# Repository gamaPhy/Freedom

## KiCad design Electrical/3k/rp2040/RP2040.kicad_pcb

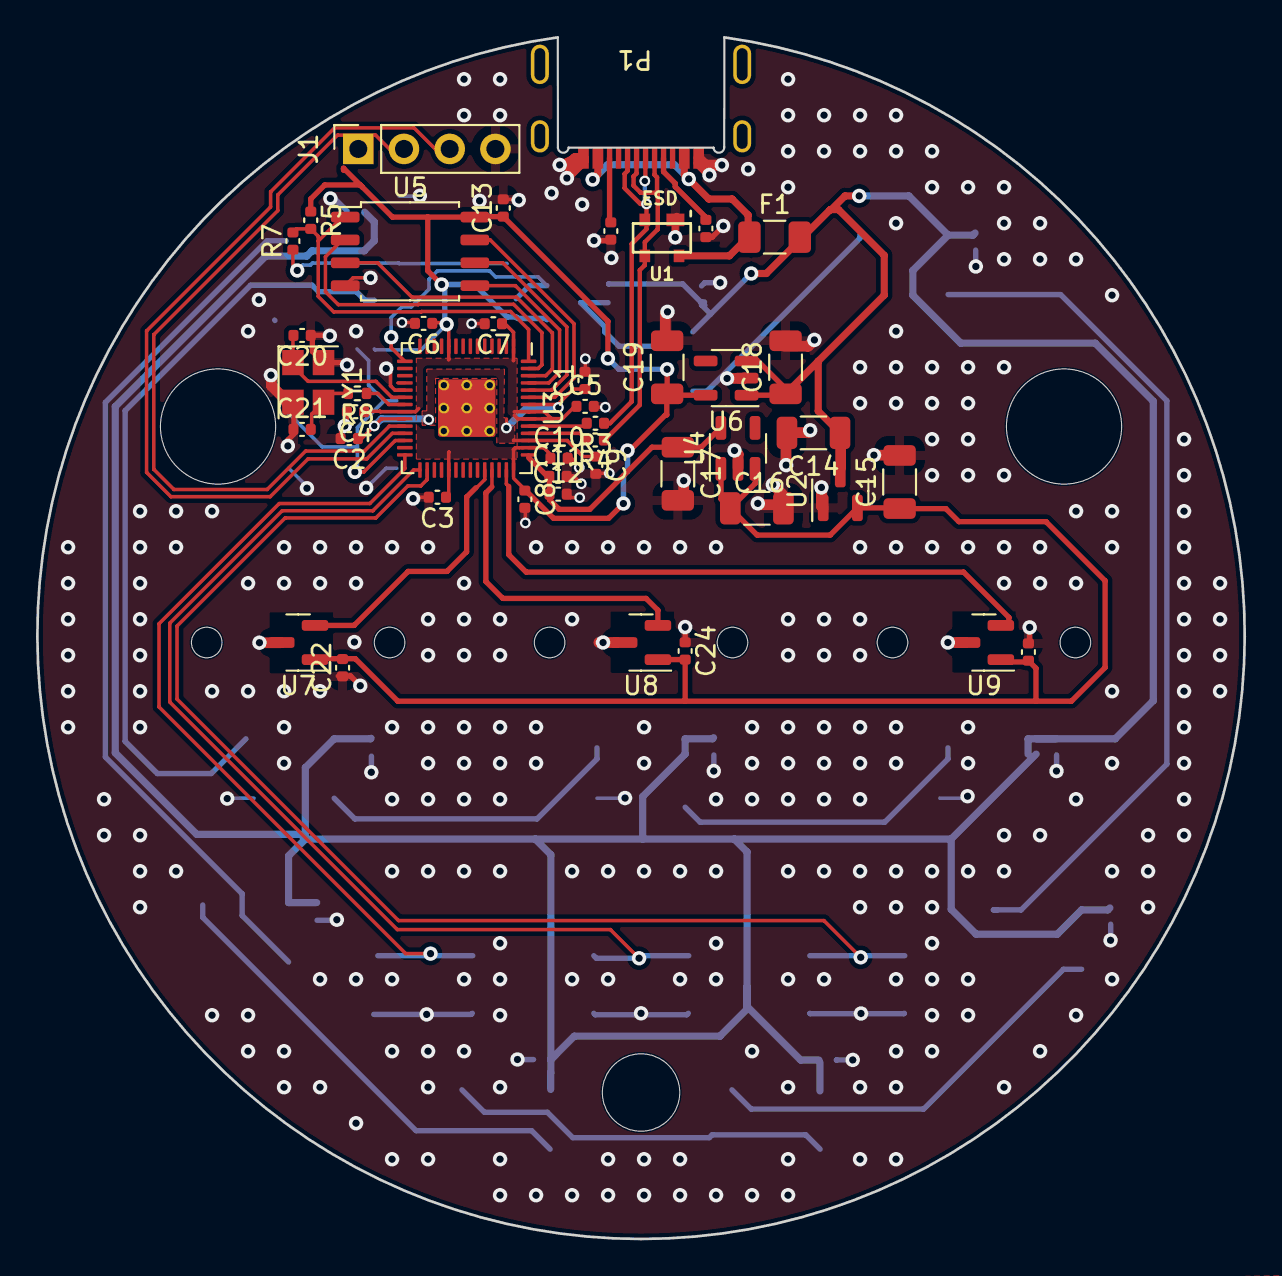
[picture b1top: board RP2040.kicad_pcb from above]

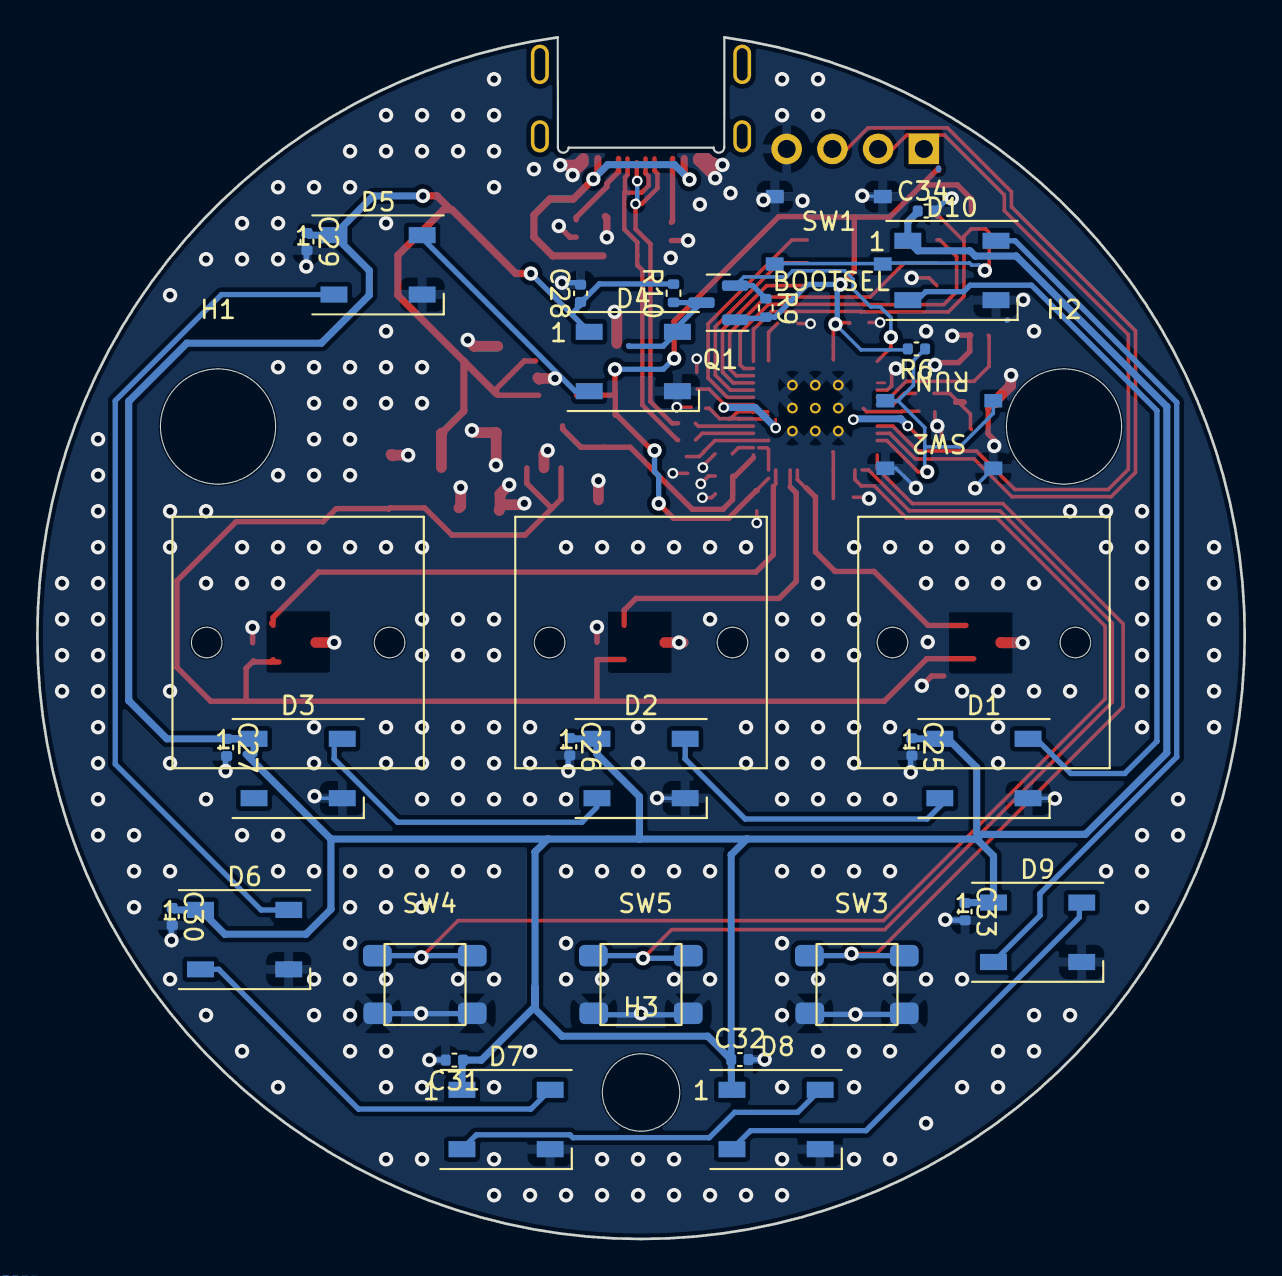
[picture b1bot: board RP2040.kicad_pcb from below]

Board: 4 copper layers, 67.1 x 66.8 mm, 76 parts (32 on the bottom side), 43 nets.

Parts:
C1, C2, C3, C4, C5, C6, C7, C8, C13, C22, C23, C24, C25, C26, C27, C28, C29, C30, C31, C32, C33, C34: 100n; C_0402_1005Metric
C9, C10, C12: 1u; C_0402_1005Metric
C11: 10n; C_0402_1005Metric
C14, C15, C16, C17, C18, C19: 10u; C_1206_3216Metric
C20, C21: 27p; C_0402_1005Metric
D1, D2, D3, D4, D5, D6, D7, D8, D9, D10: WS2812B; LED_WS2812B_PLCC4_5.0x5.0mm_P3.2mm
F1: nSMD050-24V; Fuse_1206_3216Metric
H1, H2: MountingHole_6.4mm_M6_DIN965
H3: MountingHole_4.3mm_M4_DIN965
J1: Conn_01x04_Socket; PinSocket_1x04_P2.54mm_Vertical
P1: USB-TYPE-C-016; USB-TYPE-C-016_Receptacle_DEALON_16P_MidMnt
Q1: BSS138; SOT-23
R1, R2: 5.1k; C_0402_1005Metric
R3, R4: 27R; C_0402_1005Metric
R5: 10k; C_0402_1005Metric
R6, R7: 1k; C_0402_1005Metric
R8: 47; R_0402_1005Metric
R9, R10: 10k; R_0402_1005Metric
SW1, SW2: TS-1187A-B-A-B; TS-1187A
SW3: BUTT1; PTS647_4.5x4.5mm
SW4: BUTT3; PTS647_4.5x4.5mm
SW5: BUTT2; PTS647_4.5x4.5mm
U1: PRTR5V0U2X; SOT-143B
U2: ME6208A44M3G; SOT-23
U3: RP2040; RP2040-QFN-56
U4: ME6212C25M5G; SOT-23-5
U5: W25Q16JVSS; SOIC-8_5.23x5.23mm_P1.27mm
U6: ME6212C33M5G; SOT-23-5
U7, U8, U9: SLSS49E; SOT-23
Y1: 12MHz; Crystal_SMD_3225-4Pin_3.2x2.5mm

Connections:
+1V1: C1.1, C2.1, C9.1, U3.23 (DVDD), U3.45 (VREG_VOUT), U3.50 (DVDD)
+3V3: C3.1, C4.1, C5.1, C6.1, C7.1, C8.1, C10.1, C13.1, C19.1, J1.1, Q1.1 (G), R5.1, R6.2, R9.2, U3.1 (IOVDD), U3.10 (IOVDD), U3.22 (IOVDD), U3.33 (IOVDD), U3.42 (IOVDD), U3.44 (VREG_IN), U3.48 (USB_VDD), U3.49 (IOVDD), U5.8 (VCC), U6.5 (VOUT)
+4V4: C15.1, C16.1, C22.2, C23.2, C24.2, U2.2 (VO), U4.1 (VIN), U4.3 (EN), U7.1 (VCC), U8.1 (VCC), U9.1 (VCC)
+5V: C14.1, C18.1, C25.1, C26.1, C27.1, C28.1, C29.1, C30.1, C31.1, C32.1, C33.1, C34.1, D1.1 (VDD), D2.1 (VDD), D3.1 (VDD), D4.1 (VDD), D5.1 (VDD), D6.1 (VDD), D7.1 (VDD), D8.1 (VDD), D9.1 (VDD), D10.1 (VDD), F1.2, R10.2, U2.3 (VI), U6.1 (VIN), U6.3 (EN)
/QSPI_SCLK: U3.52 (QSPI_SCLK), U5.6 (CLK)
/QSPI_SD0: U3.53 (QSPI_SD0), U5.5 (DI(IO0))
/QSPI_SD1: U3.55 (QSPI_SD1), U5.2 (DO(IO1))
/QSPI_SD2: U3.54 (QSPI_SD2), U5.3 (IO2)
/QSPI_SD3: U3.51 (QSPI_SD3), U5.7 (IO3)
/QSPI_SS: R5.2, R7.2, U3.56 (QSPI_SS), U5.1 (~CS)
ADC_AVDD: C11.1, C12.1, C17.1, U3.43 (ADC_AVDD), U4.5 (VOUT)
ADC_IN1: U3.38 (GPIO26_ADC0), U7.2 (VOUT)
ADC_IN2: U3.39 (GPIO27_ADC1), U8.2 (VOUT)
ADC_IN3: U3.41 (GPIO29_ADC3), U9.2 (VOUT)
BUTT0: SW3.1, U3.28 (GPIO17)
BUTT1: SW5.1, U3.29 (GPIO18)
BUTT2: SW4.1, U3.30 (GPIO19)
GND: C1.2, C2.2, C3.2, C4.2, C5.2, C6.2, C7.2, C8.2, C9.2, C10.2, C11.2, C12.2, C13.2, C14.2, C15.2, C16.2, C17.2, C18.2, C19.2, C20.1, C21.1, C22.1, C23.1, C24.1, C25.2, C26.2, C27.2, C28.2, C29.2, C30.2, C31.2, C32.2, C33.2, C34.2, D1.3 (VSS), D2.3 (VSS), D3.3 (VSS), D4.3 (VSS), D5.3 (VSS), D6.3 (VSS), D7.3 (VSS), D8.3 (VSS), D9.3 (VSS), D10.3 (VSS), J1.4, P1.A1 (GND), P1.A12 (GND), P1.B1 (GND), P1.B12 (GND), R1.2, R2.2, SW1.1, SW2.1, SW3.2, SW4.2, SW5.2, U1.1 (GND), U2.1 (GND), U3.19 (TESTEN), U3.57 (GND), U4.2 (GND), U5.4 (GND), U6.2 (GND), U7.3 (GND), U8.3 (GND), U9.3 (GND), Y1.2, Y1.4
LED_D: Q1.2 (S), R9.1, U3.15 (GPIO12)
unnamed: C21.2, R8.2, Y1.3
unnamed: D1.2 (DOUT), D2.4 (DIN)
unnamed: D2.2 (DOUT), D3.4 (DIN)
unnamed: D4.4 (DIN), Q1.3 (D), R10.1
unnamed: D4.2 (DOUT), D5.4 (DIN)
unnamed: D5.2 (DOUT), D6.4 (DIN)
unnamed: D6.2 (DOUT), D7.4 (DIN)
unnamed: D7.2 (DOUT), D8.4 (DIN)
unnamed: D8.2 (DOUT), D9.4 (DIN)
unnamed: D9.2 (DOUT), D10.4 (DIN)
unnamed: P1.A5 (CC1), R1.1
unnamed: P1.B5 (CC2), R2.1
unnamed: R7.1, SW1.2
unnamed: R6.1, SW2.2, U3.26 (RUN)
unnamed: R4.2, U3.46 (USB_DM)
unnamed: R3.2, U3.47 (USB_DP)
OSC_IN: C20.2, U3.20 (XIN), Y1.1
OSC_OUT: R8.1, U3.21 (XOUT)
SWCLK: J1.2, U3.24 (SWCLK)
SWDIO: J1.3, U3.25 (SWD)
UG_DIN: D1.4 (DIN), D10.2 (DOUT)
USB_D+: P1.A6 (D+), P1.B6 (D+), R3.1, U1.2 (I/O1)
USB_D-: P1.A7 (D-), P1.B7 (D-), R4.1, U1.3 (I/O2)
VBUS: F1.1, P1.A4 (VBUS), P1.A9 (VBUS), P1.B4 (VBUS), P1.B9 (VBUS), U1.4 (VCC)

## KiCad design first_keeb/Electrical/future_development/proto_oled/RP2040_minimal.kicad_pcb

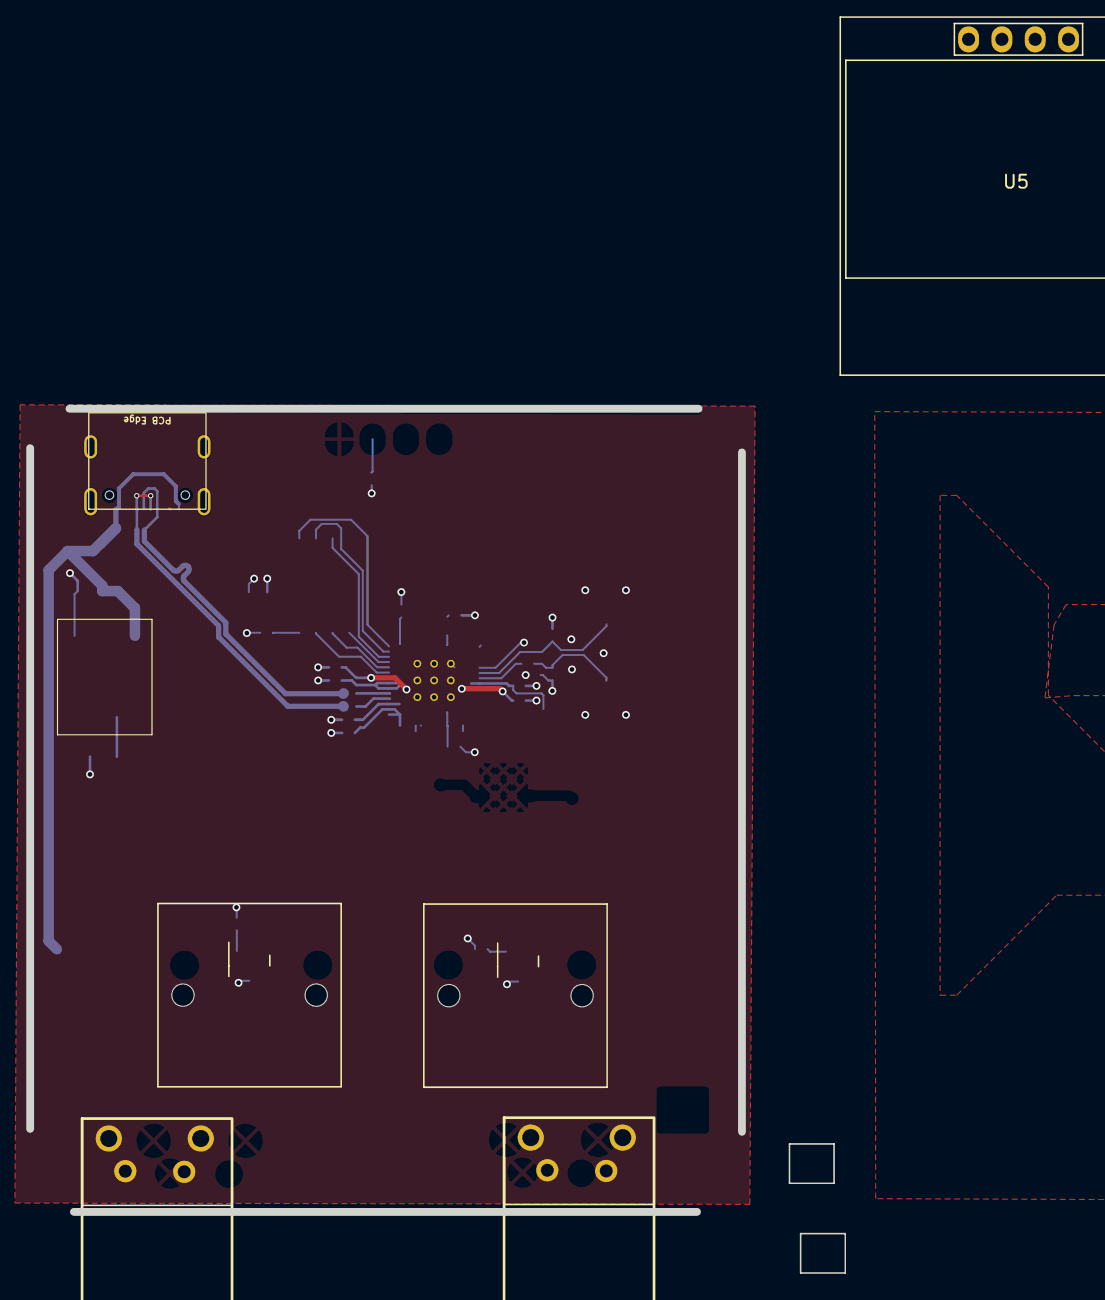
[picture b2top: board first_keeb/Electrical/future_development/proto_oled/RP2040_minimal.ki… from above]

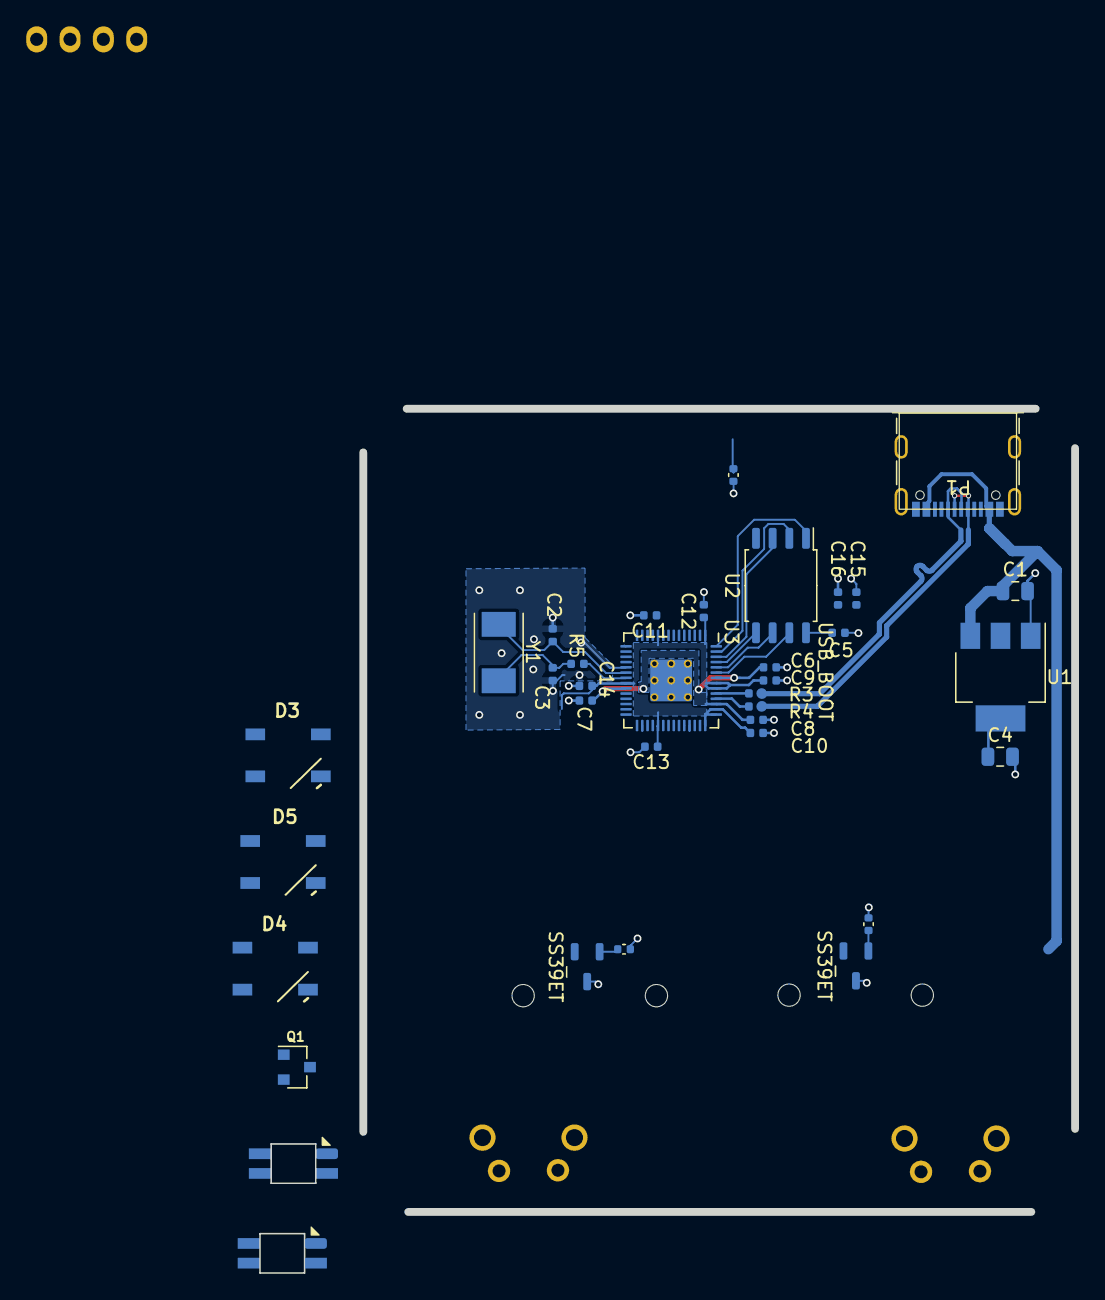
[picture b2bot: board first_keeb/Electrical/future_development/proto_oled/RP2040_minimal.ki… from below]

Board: 2 copper layers, 62.1 x 65.9 mm, 38 parts (35 on the bottom side), 21 nets.

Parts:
C1, C4: 10u; C_0805_2012Metric
C2, C3: 27p; C_0402_1005Metric
C5, C6, C7, C9, C11, C12, C13, C14, C15, C16: 100n; C_0402_1005Metric
C8, C10: 1u; C_0402_1005Metric
C21, C22, C23: C_0402_1005Metric
D1, D2: SK6812-MINI-E
D3, D4, D5: WS2812B
P1: USB_C_Receptacle_GCT_USB4105-xx-A_16P_TopMnt_Hori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; USB_C_Receptacle_GCT_USB4105-xx-A_16P_TopMnt_Horizontal
Q1: SOT-23
R3, R4: 27; C_0402_1005Metric
R5: 1k; C_0402_1005Metric
S1, S1#2: SS39ET; SOT-23-3
SW1, SW2: 2-1825027-0_Right_Angle_Switch-9.24mm_Stem; 2-1825027-0_Right_Angle_Button
U1: NCP1117-3.3_SOT223; SOT-223-3_TabPin2
U2: W25Q128JVS; SOIC-8_5.23x5.23mm_P1.27mm
U3: RP2040; RP2040-QFN-56
U5: 128x64OLED
Y1: ABLS-12.000MHZ-B4-T; Crystal_SMD_Abracon_ABM7-2Pin_6.0x3.5mm

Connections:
+1V1: C6.1, C7.1, C8.1, U3.23, U3.45, U3.50
+3V3: C4.1, C5.1, C9.1, C10.1, C11.1, C12.1, C13.1, C14.1, C15.1, C16.1, C21.1, C22.1, C23.1, S1.1, S1#2.1, U1.2, U2.8, U3.1, U3.10, U3.22, U3.33, U3.42, U3.43, U3.44, U3.48, U3.49, U5.2
/GPIO18: SW2.2, U3.29
/GPIO19: SW1.2, U3.30
/GPIO26_ADC0: S1.2, U3.38
/GPIO27_ADC1: S1#2.2, U3.39
/QSPI_SCLK: U2.6, U3.52
/QSPI_SD0: U2.5, U3.53
/QSPI_SD1: U2.2, U3.55
/QSPI_SD2: U2.3, U3.54
/QSPI_SD3: U2.7, U3.51
/QSPI_SS: U2.1, U3.56
/USB_D+: P1.A6, P1.B6, R3.1
/USB_D-: P1.A7, P1.B7, R4.1
/XIN: C2.1, U3.20, Y1.1
/XOUT: R5.1, U3.21
GND: C1.2, C2.2, C3.2, C4.2, C5.2, C6.2, C7.2, C8.2, C9.2, C10.2, C11.2, C12.2, C13.2, C14.2, C15.2, C16.2, C21.2, C22.2, C23.2, D3.3, D4.3, D5.3, P1.A1, P1.A12, P1.B1, P1.B12, S1.3, S1#2.3, SW1.1, SW1.3, SW1.4, SW2.1, SW2.3, SW2.4, U1.1, U2.4, U3.19, U3.57, U5.1
unnamed: C3.1, R5.2, Y1.2
unnamed: R3.2, U3.47
unnamed: R4.2, U3.46
VBUS: C1.1, D3.1, D4.1, D5.1, P1.A4, P1.A9, P1.B4, P1.B9, U1.3

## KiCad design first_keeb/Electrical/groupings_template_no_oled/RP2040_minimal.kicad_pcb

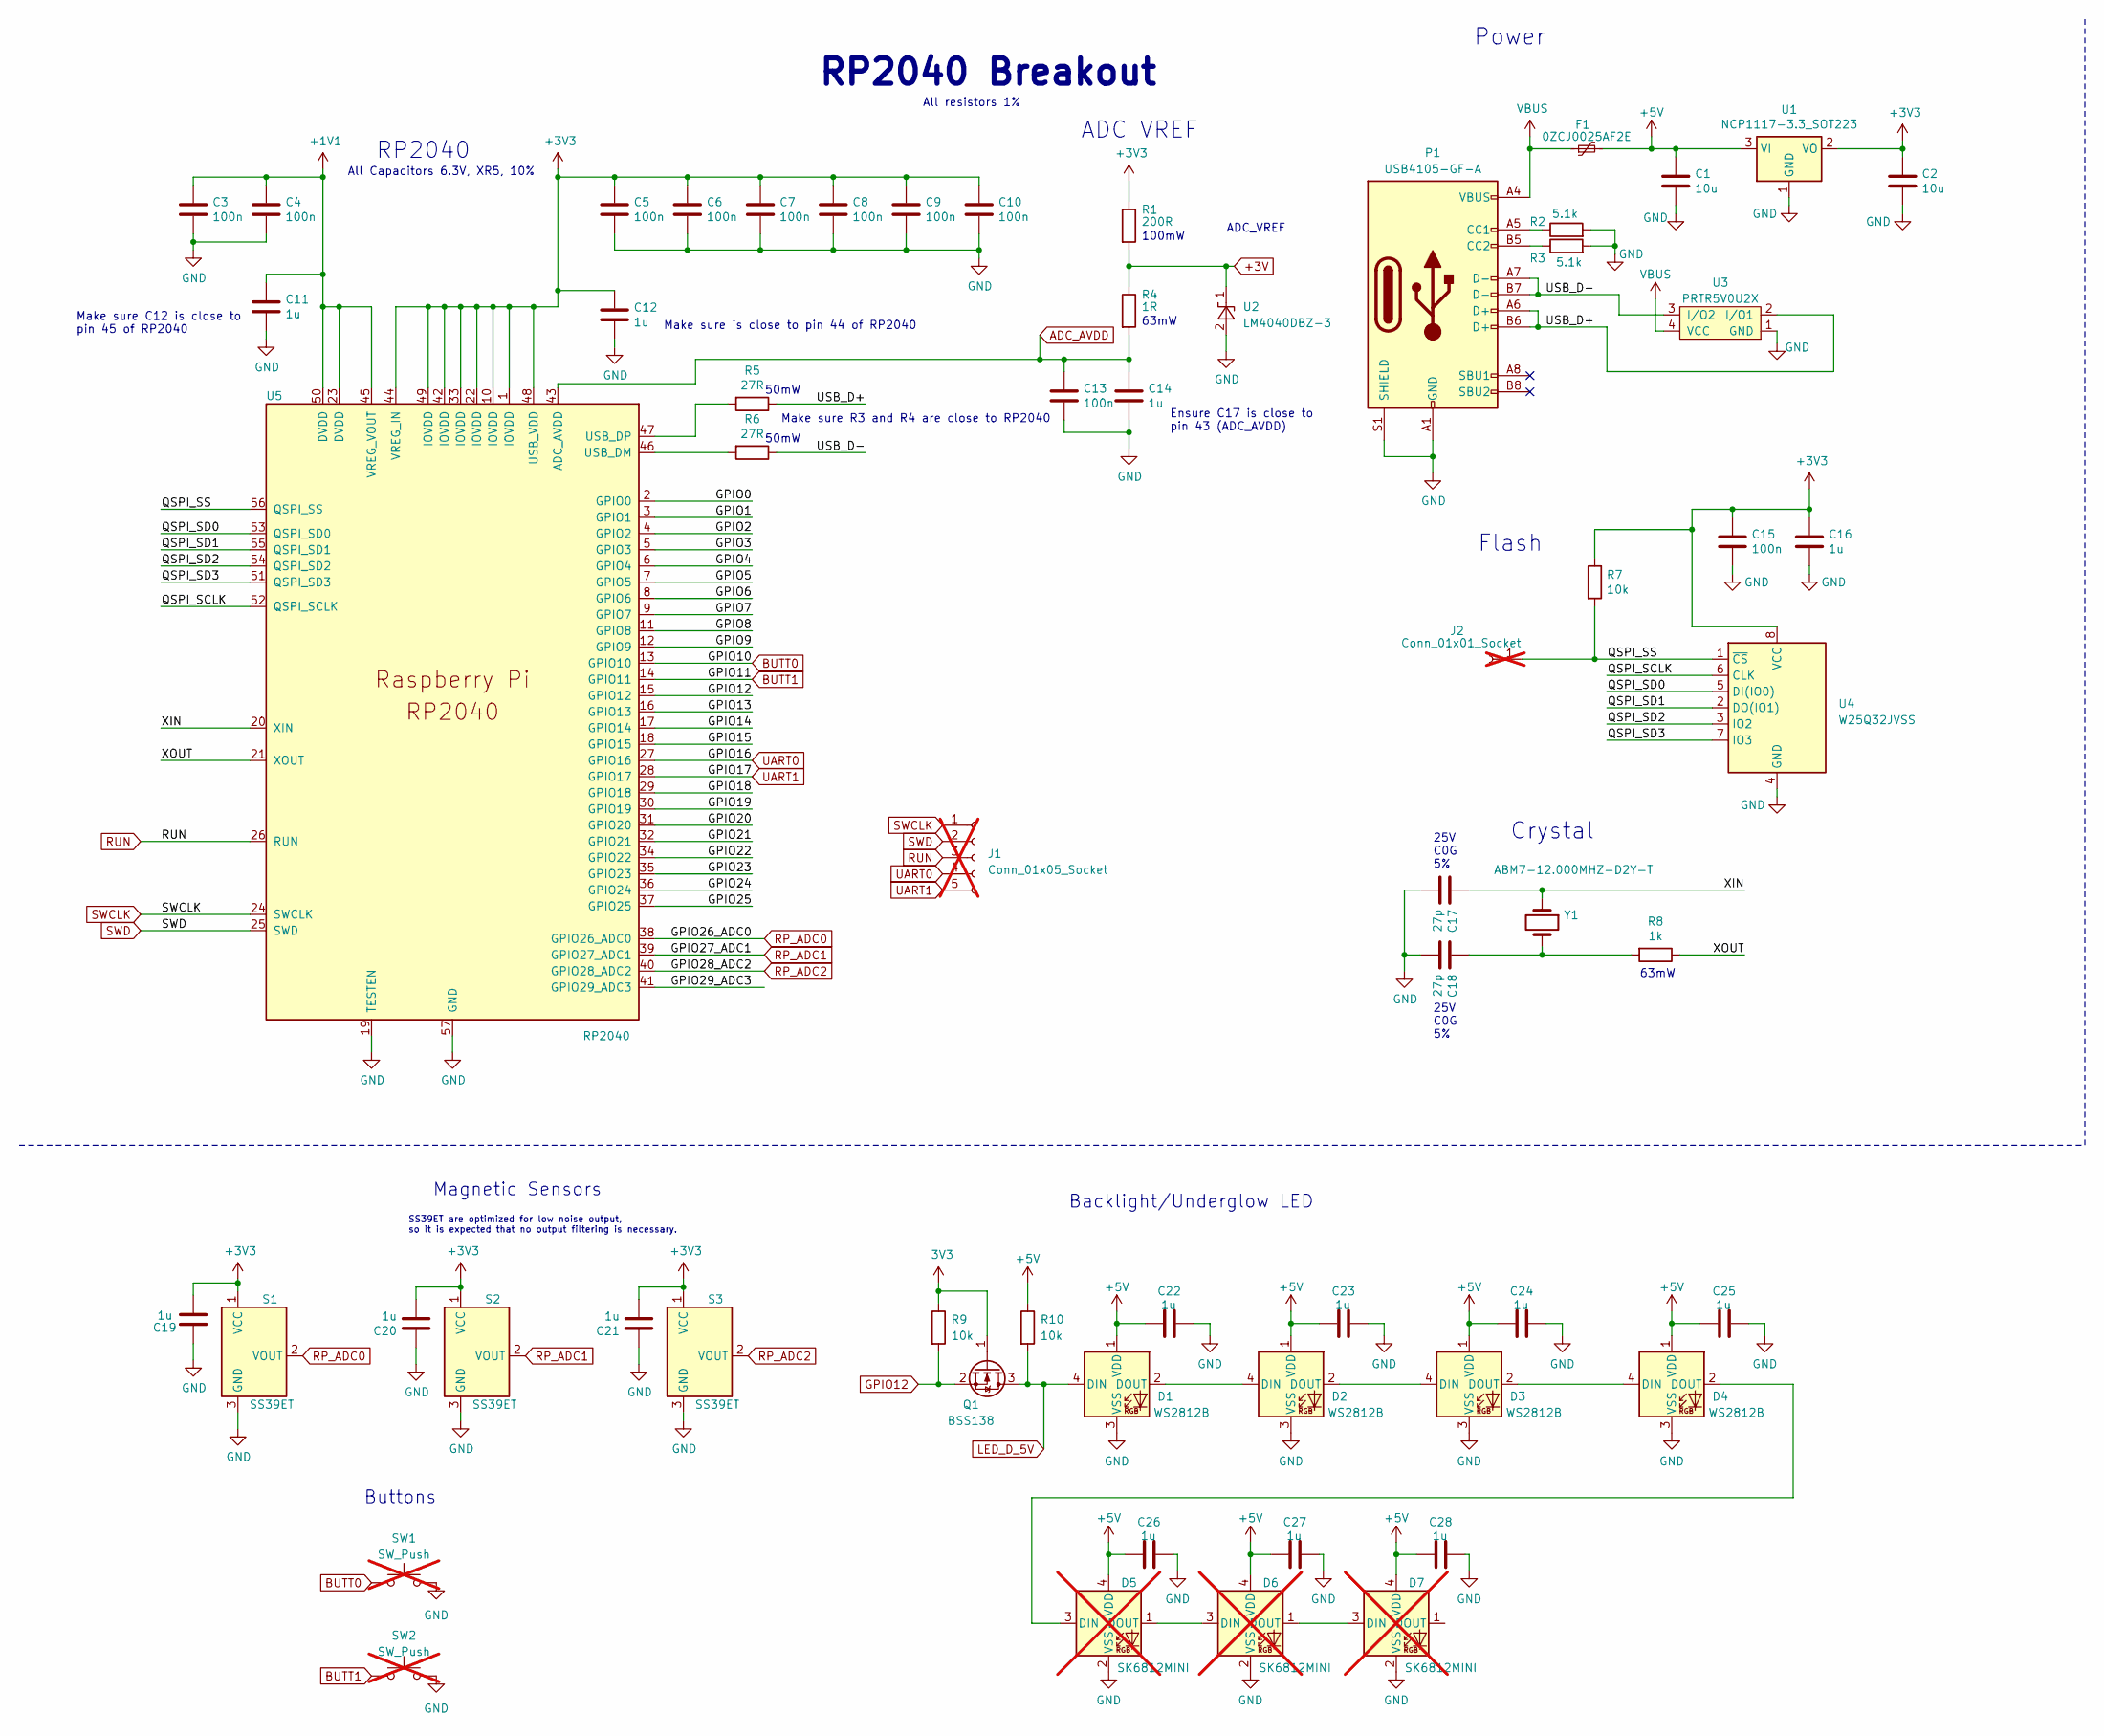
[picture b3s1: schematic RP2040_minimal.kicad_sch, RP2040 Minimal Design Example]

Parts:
C1, C2: 10u; C_0805_2012Metric
C3, C4, C5, C6, C7, C8, C9, C10, C13, C15: 100n; C_0402_1005Metric
C11, C12, C14, C16, C19, C20, C21, C22, C23, C24, C25, C26, C27, C28: 1u; C_0402_1005Metric
C17, C18: 27p; C_0402_1005Metric
D1, D2, D3, D4: WS2812B; LED_WS2812B_PLCC4_5.0x5.0mm_P3.2mm
D5, D6, D7: SK6812MINI; LED_SK6812MINI_PLCC4_3.5x3.5mm_P1.75mm; not fitted
F1: 0ZCJ0025AF2E; Fuse_1206_3216Metric
J1: Conn_01x05_Socket; PinSocket_1x05_P2.54mm_Vertical; not fitted
J2: Conn_01x01_Socket; PinSocket_1x01_P2.54mm_Vertical; not fitted
P1: USB4105-GF-A; USB_C_Receptacle_GCT_USB4105-xx-A_16P_TopMnt_Horizontal
Q1: BSS138; SOT-23
R1: 200R; C_0603_1608Metric
R2, R3: 5.1k; C_0402_1005Metric
R4: 1R; C_0603_1608Metric
R5, R6: 27R; C_0402_1005Metric
R7, R9, R10: 10k; C_0402_1005Metric
R8: 1k; C_0402_1005Metric
S1, S2, S3: SS39ET; SOT-23-3
SW1, SW2: SW_Push; SW_Push_1P1T_NO_6x6mm_H9.5mm; not fitted
U1: NCP1117-3.3_SOT223; SOT-223-3_TabPin2
U2: LM4040DBZ-3; SOT-23
U3: PRTR5V0U2X; SOT-143
U4: W25Q32JVSS; SOIC-8_5.23x5.23mm_P1.27mm
U5: RP2040; RP2040-QFN-56
Y1: ABM7-12.000MHZ-D2Y-T; Crystal_SMD_Abracon_ABM7-2Pin_6.0x3.5mm

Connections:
+1V1: C3.1, C4.1, C11.1, U5.23 (DVDD), U5.45 (VREG_VOUT), U5.50 (DVDD)
+3V: R1.2, R4.1, U2.1 (K)
+5V: C1.1, C22.1, C23.1, C24.1, C25.1, C26.1, C27.1, C28.1, D1.1 (VDD), D2.1 (VDD), D3.1 (VDD), D4.1 (VDD), D5.4 (VDD), D6.4 (VDD), D7.4 (VDD), F1.2, R10.1, U1.3 (VI)
/GPIO0: U5.2 (GPIO0)
/GPIO1: U5.3 (GPIO1)
/GPIO2: U5.4 (GPIO2)
/GPIO3: U5.5 (GPIO3)
/GPIO4: U5.6 (GPIO4)
/GPIO5: U5.7 (GPIO5)
/GPIO6: U5.8 (GPIO6)
/GPIO7: U5.9 (GPIO7)
/GPIO8: U5.11 (GPIO8)
/GPIO9: U5.12 (GPIO9)
/GPIO13: U5.16 (GPIO13)
/GPIO14: U5.17 (GPIO14)
/GPIO15: U5.18 (GPIO15)
/GPIO18: U5.29 (GPIO18)
/GPIO19: U5.30 (GPIO19)
/GPIO20: U5.31 (GPIO20)
/GPIO21: U5.32 (GPIO21)
/GPIO22: U5.34 (GPIO22)
/GPIO23: U5.35 (GPIO23)
/GPIO24: U5.36 (GPIO24)
/GPIO25: U5.37 (GPIO25)
/GPIO29_ADC3: U5.41 (GPIO29_ADC3)
/QSPI_SCLK: U4.6 (CLK), U5.52 (QSPI_SCLK)
/QSPI_SD0: U4.5 (DI(IO0)), U5.53 (QSPI_SD0)
/QSPI_SD1: U4.2 (DO(IO1)), U5.55 (QSPI_SD1)
/QSPI_SD2: U4.3 (IO2), U5.54 (QSPI_SD2)
/QSPI_SD3: U4.7 (IO3), U5.51 (QSPI_SD3)
/QSPI_SS: J2.1, R7.2, U4.1 (~CS), U5.56 (QSPI_SS)
/USB_D+: P1.A6 (D+), P1.B6 (D+), R5.1, U3.2 (I/O1)
/USB_D-: P1.A7 (D-), P1.B7 (D-), R6.1, U3.3 (I/O2)
/XIN: C17.1, U5.20 (XIN), Y1.1
/XOUT: R8.1, U5.21 (XOUT)
ADC_AVDD: C13.1, C14.1, R4.2, U5.43 (ADC_AVDD)
BUTT0: SW1.1, U5.13 (GPIO10)
BUTT1: SW2.1, U5.14 (GPIO11)
GND: C1.2, C2.2, C3.2, C4.2, C5.2, C6.2, C7.2, C8.2, C9.2, C10.2, C11.2, C12.2, C13.2, C14.2, C15.2, C16.2, C17.2, C18.2, C19.1, C20.1, C21.1, C22.2, C23.2, C24.2, C25.2, C26.2, C27.2, C28.2, D1.3 (VSS), D2.3 (VSS), D3.3 (VSS), D4.3 (VSS), D5.2 (VSS), D6.2 (VSS), D7.2 (VSS), P1.A1 (GND), P1.A12 (GND), P1.B1 (GND), P1.B12 (GND), P1.S1 (SHIELD), R2.2, R3.2, S1.3 (GND), S2.3 (GND), S3.3 (GND), SW1.2, SW2.2, U1.1 (GND), U2.2 (A), U3.1 (GND), U4.4 (GND), U5.19 (TESTEN), U5.57 (GND)
GPIO12: Q1.2 (S), R9.2, U5.15 (GPIO12)
LED_D_5V: D1.4 (DIN), Q1.3 (D), R10.2
unnamed: C18.1, R8.2, Y1.2
unnamed: D1.2 (DOUT), D2.4 (DIN)
unnamed: D2.2 (DOUT), D3.4 (DIN)
unnamed: D3.2 (DOUT), D4.4 (DIN)
unnamed: D4.2 (DOUT), D5.3 (DIN)
unnamed: D5.1 (DOUT), D6.3 (DIN)
unnamed: D6.1 (DOUT), D7.3 (DIN)
unnamed: P1.A5 (CC1), R2.1
unnamed: P1.B5 (CC2), R3.1
unnamed: R6.2, U5.46 (USB_DM)
unnamed: R5.2, U5.47 (USB_DP)
RP_ADC0: S1.2 (VOUT), U5.38 (GPIO26_ADC0)
RP_ADC1: S2.2 (VOUT), U5.39 (GPIO27_ADC1)
RP_ADC2: S3.2 (VOUT), U5.40 (GPIO28_ADC2)
RUN: J1.3, U5.26 (RUN)
SWCLK: J1.1, U5.24 (SWCLK)
SWD: J1.2, U5.25 (SWD)
VBUS: F1.1, P1.A4 (VBUS), P1.A9 (VBUS), P1.B4 (VBUS), P1.B9 (VBUS), U3.4 (VCC)

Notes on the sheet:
RP2040 Breakout
All Capacitors 6.3V, XR5, 10%
Make sure C12 is close to pin 45 of RP2040
ADC VREF
63mW
25V C0G 5%
ADC_VREF
Make sure R3 and R4 are close to RP2040
Magnetic Sensors
Backlight/Underglow LED
RP2040
SS39ET are optimized for low noise output, so it is expected that no output filtering is necessary.
Power
Buttons
Crystal
Make sure is close to pin 44 of RP2040
All resistors 1%
50mW
Flash
Ensure C17 is close to pin 43 (ADC_AVDD)
100mW

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
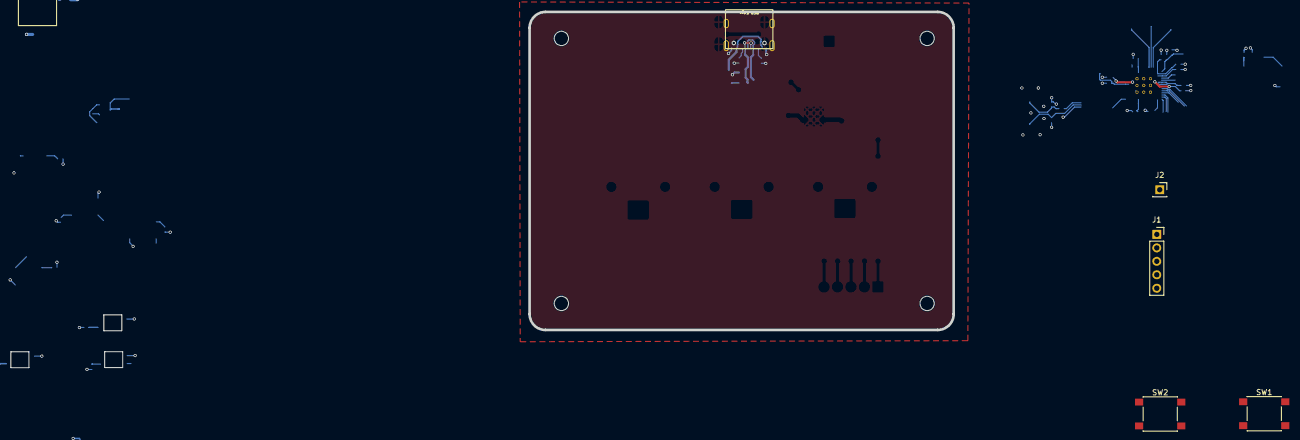
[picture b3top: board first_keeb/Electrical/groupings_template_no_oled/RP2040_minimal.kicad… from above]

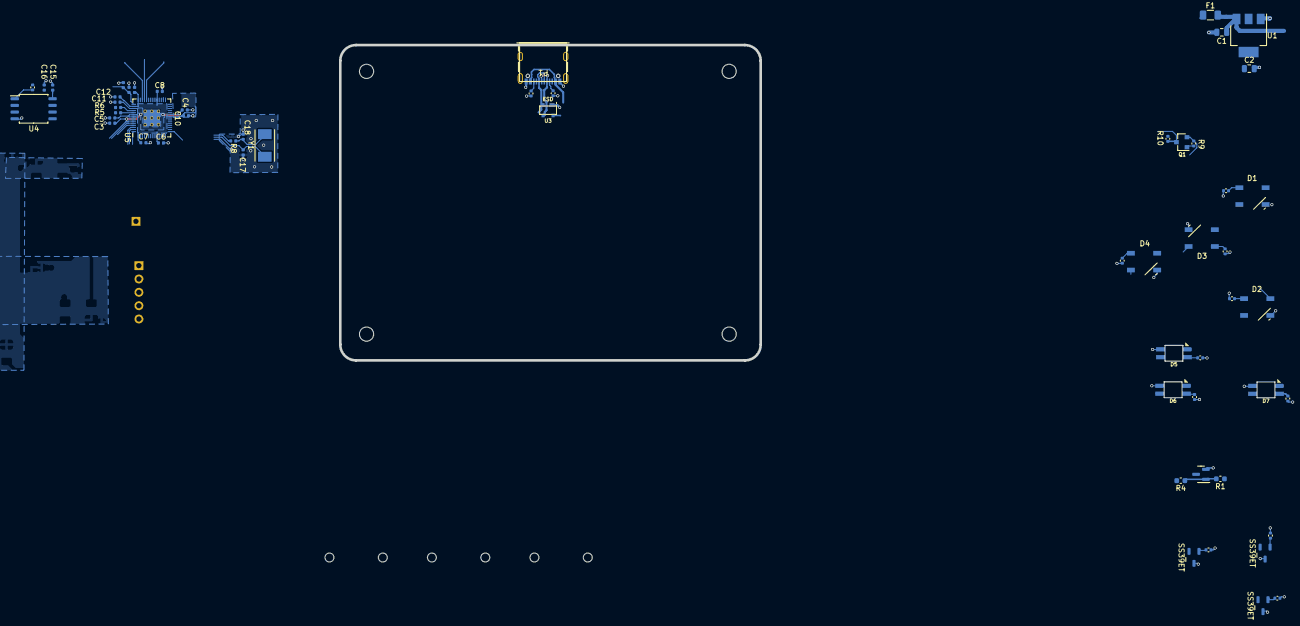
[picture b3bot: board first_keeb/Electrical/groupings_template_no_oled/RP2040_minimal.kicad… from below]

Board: 2 copper layers, 61 parts (57 on the bottom side), 38 nets.

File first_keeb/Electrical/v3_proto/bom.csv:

"Comment All resistor at least 1%, and >=100mW All capacitor at least 5%, and >= 6.3 V ",Designator,Footprint
10uF,"C1, C2",Capacitor_SMD:C_0805_2012Metric
100nF,"C3, C4, C5, C6, C7, C8, C9, C10, C13, C15",Capacitor_SMD:C_0402_1005Metric
1uF,"C11, C12, C14, C16, C19, C20, C21, C22, C23, C24, C25, C26, C27, C28",Capacitor_SMD:C_0402_1005Metric
27pF,"C17, C18",Capacitor_SMD:C_0402_1005Metric
WS2812B,"D1, D2, D3, D4",LED_SMD:LED_WS2812B_PLCC4_5.0x5.0mm_P3.2mm
0ZCJ0025AF2E,F1,Fuse:Fuse_1206_3216Metric
USB4105-GF-A,P1,Connector_USB:USB_C_Receptacle_GCT_USB4105-xx-A_16P_TopMnt_Horizontal
BSS138,Q1,Package_TO_SOT_SMD:SOT-23
200 Ohm,R1,Capacitor_SMD:C_0603_1608Metric
5.1k,"R2, R3",Capacitor_SMD:C_0402_1005Metric
1 Ohm,R4,Capacitor_SMD:C_0603_1608Metric
27 Ohm ,"R5, R6",Capacitor_SMD:C_0402_1005Metric
10k,"R7, R9, R10",Capacitor_SMD:C_0402_1005Metric
1k,R8,Capacitor_SMD:C_0402_1005Metric
SS39ET,"S1, S2, S3",Package_TO_SOT_SMD:SOT-23-3
NCP1117-3.3_SOT223,U1,Package_TO_SOT_SMD:SOT-223-3_TabPin2
LM4040DBZ-3,U2,Package_TO_SOT_SMD:SOT-23
PRTR5V0U2X,U3,Package_TO_SOT_SMD:SOT-143
W25Q32JVSS,U4,Package_SO:SOIC-8_5.23x5.23mm_P1.27mm
RP2040,U5,RP2040_minimal:RP2040-QFN-56
ABM7-12.000MHZ-D2Y-T,Y1,Crystal:Crystal_SMD_Abracon_ABM7-2Pin_6.0x3.5mm
